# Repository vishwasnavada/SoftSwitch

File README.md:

# SoftSwitch
Opensource SoftSwitch for DC and AC applications

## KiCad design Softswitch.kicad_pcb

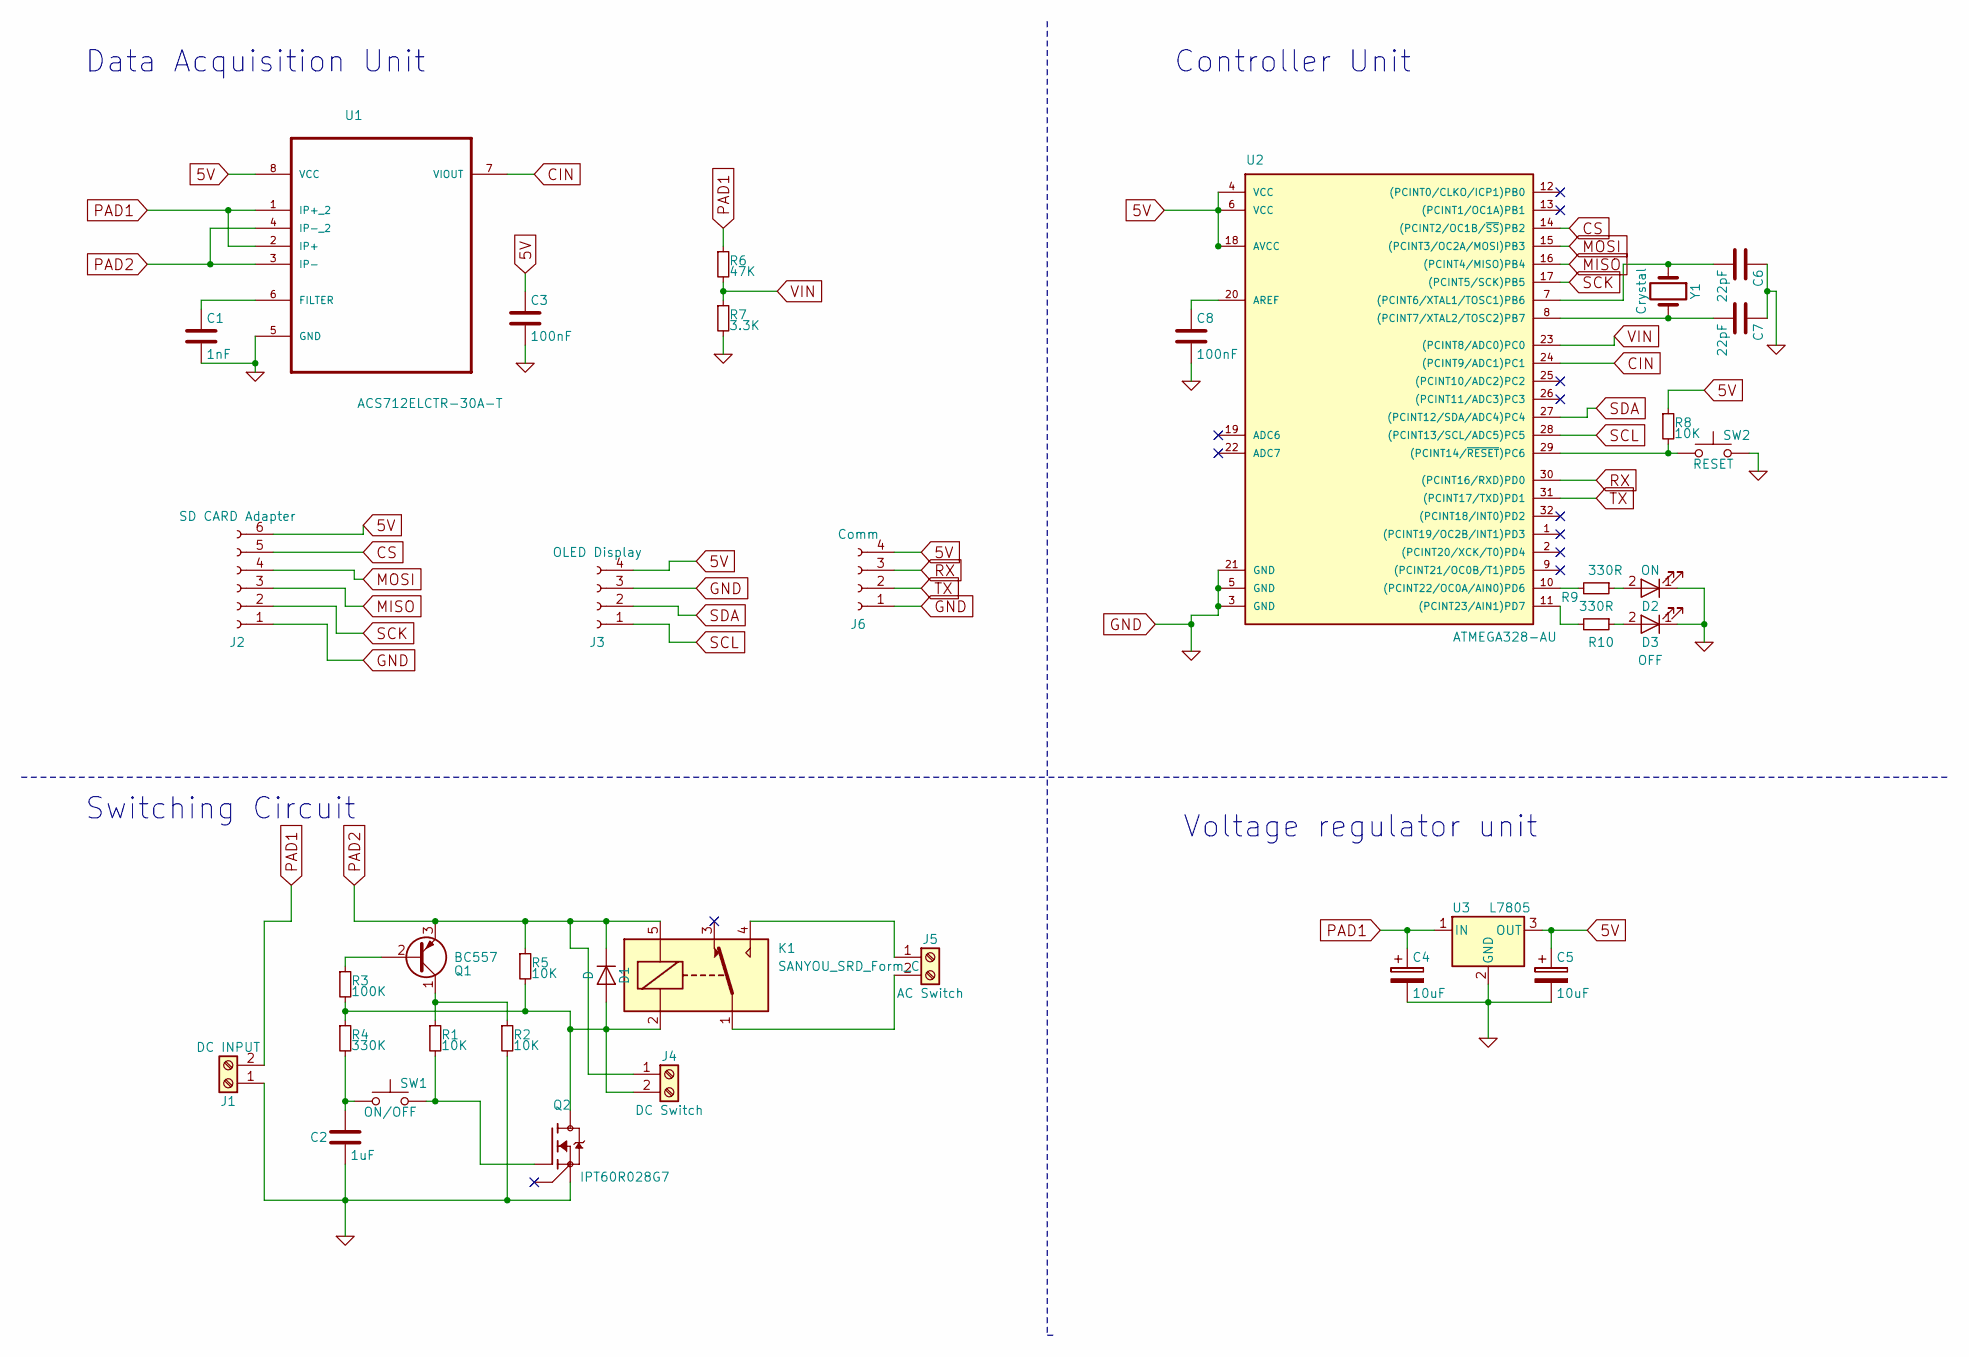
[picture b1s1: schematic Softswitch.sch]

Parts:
C1: 1nF; C_0603
C2: 1uF; C_0603
C3, C8: 100nF; C_0603
C4, C5: 10uF; CP_Tantalum_Case-A_EIA-3216-18_Hand
C6, C7: 22pF; C_0603
D1: D; D_1206
D2: ON; LED_5mm_Radial
D3: OFF; LED_5mm_Radial
J1: DC INPUT; TerminalBlock_bornier-2_P5.08mm
J2: SD CARD Adapter; Socket_Strip_Angled_1x06_Pitch2.54mm
J3: OLED Display; Socket_Strip_Straight_1x04_Pitch2.54mm
J4: DC Switch; TerminalBlock_bornier-2_P5.08mm
J5: AC Switch; TerminalBlock_bornier-2_P5.08mm
J6: Comm; Socket_Strip_Straight_1x04_Pitch2.54mm
K1: SANYOU_SRD_Form_C; Relay_SPDT_SANYOU_SRD_Series_Form_C
Q1: BC557; TO-92_Molded_Narrow
Q2: IPT60R028G7; TRANS_IPT60R028G7XTMA1
R1, R2, R5, R8: 10K; R_0603
R3: 100K; R_0603
R4: 330K; R_0603
R6: 47K; R_0603
R7: 3.3K; R_0603
R9, R10: 330R; R_0603
SW1: ON/OFF; SW_PUSH_6mm
SW2: RESET; SW_PUSH_6mm
U1: ACS712ELCTR-30A-T; SOIC-8-N
U2: ATMEGA328-AU; TQFP-32_7x7mm_Pitch0.8mm
U3: L7805; TO-252-3
Y1: Crystal; Crystal_HC52-8mm_Vertical

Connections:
5V: C3.1, C5.1, J2.6, J3.4, J6.4, R8.1, U1.8 (VCC), U2.4 (VCC), U2.6 (VCC), U2.18 (AVCC), U3.3 (OUT)
CIN: U1.7 (VIOUT), U2.24 ((PCINT9/ADC1)PC1)
CS: J2.5, U2.14 ((PCINT2/OC1B/~SS~)PB2)
GND: C1.2, C2.2, C3.2, C4.2, C5.2, C6.1, C7.1, C8.2, D2.1 (K), D3.1 (K), J1.1, J2.1, J3.3, J6.1, Q2.3 (SOURCE), Q2.4 (SOURCE), Q2.5 (SOURCE), Q2.6 (SOURCE), Q2.7 (SOURCE), Q2.8 (SOURCE), R2.2, R7.2, SW2.2, U1.5 (GND), U2.3 (GND), U2.5 (GND), U2.21 (GND), U3.2 (GND)
MISO: J2.3, U2.16 ((PCINT4/MISO)PB4)
MOSI: J2.4, U2.15 ((PCINT3/OC2A/MOSI)PB3)
unnamed: C1.1, U1.6 (FILTER)
unnamed: C2.1, R4.2, SW1.1
unnamed: C6.2, U2.7 ((PCINT6/XTAL1/TOSC1)PB6), Y1.1
unnamed: C7.2, U2.8 ((PCINT7/XTAL2/TOSC2)PB7), Y1.2
unnamed: C8.1, U2.20 (AREF)
unnamed: D1.2 (A), J4.2, K1.2, Q2.9 (DRAIN), R3.2, R4.1, R5.2
unnamed: D2.2 (A), R9.1
unnamed: D3.2 (A), R10.1
unnamed: J5.1, K1.4
unnamed: J5.2, K1.1
unnamed: Q1.1 (C), R1.1, R2.1
unnamed: Q1.2 (B), R3.1
unnamed: Q2.1 (GATE), R1.2, SW1.2
unnamed: R8.2, SW2.1, U2.29 ((PCINT14/~RESET~)PC6)
unnamed: R9.2, U2.10 ((PCINT22/OC0A/AIN0)PD6)
unnamed: R10.2, U2.11 ((PCINT23/AIN1)PD7)
PAD1: C4.1, J1.2, R6.1, U1.1 (IP+_2), U1.2 (IP+), U3.1 (IN)
PAD2: D1.1 (K), J4.1, K1.5, Q1.3 (E), R5.1, U1.3 (IP-), U1.4 (IP-_2)
RX: J6.3, U2.30 ((PCINT16/RXD)PD0)
SCK: J2.2, U2.17 ((PCINT5/SCK)PB5)
SCL: J3.1, U2.28 ((PCINT13/SCL/ADC5)PC5)
SDA: J3.2, U2.27 ((PCINT12/SDA/ADC4)PC4)
TX: J6.2, U2.31 ((PCINT17/TXD)PD1)
VIN: R6.2, R7.1, U2.23 ((PCINT8/ADC0)PC0)

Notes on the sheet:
Switching Circuit
Data Acquisition Unit
Controller Unit
Voltage regulator unit

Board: 2 copper layers, 36 parts (0 on the bottom side), 30 nets, no tracks yet.
